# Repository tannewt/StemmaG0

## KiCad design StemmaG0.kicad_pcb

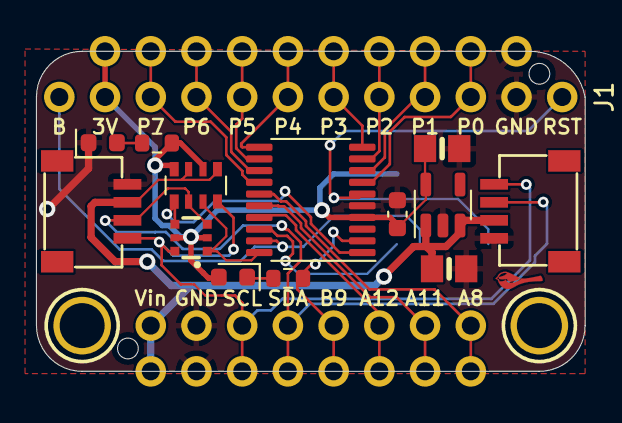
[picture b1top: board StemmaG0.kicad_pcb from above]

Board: 2 copper layers, 30.5 x 17.8 mm, 20 parts (1 on the bottom side), 24 nets.

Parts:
C1: 0.1uF; C_0603_1608Metric
C2, C3: 10uF; 0805-NO
CONN3, CONN4: SM04B-SRSS-TB; JST_SH4
D1, D2: LED_Small; LED_0603_1608Metric
J1: Conn_01x12; PinHeader_1x12_P2.54mm_Vertical
J2, J4: Conn_01x08; PinHeader_1x08_P2.54mm_Vertical
J3: Conn_ARM_JTAG_SWD_10; PinHeader_2x05_P1.27mm_Vertical_SMD
J5: Conn_01x10; PinHeader_1x10_P2.54mm_Vertical
Q2: BSS138BKS; SOT363
R1: 10K; R_0603_1608Metric
R2: R_Small; R_0603_1608Metric
R3: 10K; R_Array_Convex_4x0603
U1: STMG0x0F; TSSOP-20_4.4x6.5mm_P0.65mm
U2: AP2112K-3.3; TSOT-23-5
U$19, U$21: MOUNTINGHOLE2.5; MOUNTINGHOLE_2.5_PLATED

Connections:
3.3V: C1.1, C3.1, D2.2 (A), J1.11, J3.1 (VTref), J5.10, Q2.2 (G), Q2.5 (G), R1.1, R3.2 (1), R3.4 (1), U1.4 (VDD/VDDA), U2.5 (OUT)
/A8: J2.8, J4.8, U1.15 (PB0/PB1/PB2/PA8)
/A11: J2.7, J4.7, U1.16 (PA11[PA9])
/A12: J2.6, J4.6, U1.17 (PA12[PA10])
/B9: J2.5, J4.5, R2.2, U1.2 (PB9/PC14-OSC32_IN)
/P0: J1.3, J5.2, U1.7 (PA0)
/P1: J1.4, J5.3, U1.8 (PA1)
/P2: J1.5, J5.4, U1.9 (PA2)
/P3: J1.6, J5.5, U1.10 (PA3)
/P4: J1.7, J5.6, U1.11 (PA4)
/P5: J1.8, J5.7, U1.12 (PA5)
/P6: J1.9, J5.8, U1.13 (PA6)
/P7: J1.10, J5.9, U1.14 (PA7)
/SCL: CONN3.4 (SCL), CONN4.4 (SCL), J2.3, J4.3, Q2.6 (D), R3.8 (2)
/SCL_3V: Q2.1 (S), R3.7 (2), U1.20 (PB3/PB4/PB5/PB6/I2C1_SCL)
/SDA: CONN3.3 (SDA), CONN4.3 (SDA), J2.4, J4.4, Q2.3 (D), R3.6 (2)
/SDA_3V: Q2.4 (S), R3.5 (2), U1.1 (PB7/PB8/I2C1_SDA)
/SWCLK: J1.12, J3.4 (SWDCLK/TCK), U1.19 (PA15/PA14/SWCLK-BOOT0)
/SWDIO: J3.2 (SWDIO/TMS), U1.18 (PA13/SWDIO)
/nRST: J1.1, J3.10 (~RESET), U1.6 (NRST)
GND: C1.2, C2.2, C3.2, CONN3.1 (GND), CONN4.1 (GND), D1.1 (K), J1.2, J2.2, J3.3 (GND), J3.5 (GND), J3.9 (GNDDetect), J4.2, J5.1, U1.5 (VSS/VSSA), U2.2 (GND)
unnamed: D1.2 (A), R1.2
unnamed: D2.1 (K), R2.1
VCC: C2.1, CONN3.2 (V+), CONN4.2 (V+), J2.1, J4.1, R3.1, R3.3 (1), U2.1 (IN), U2.3 (EN)

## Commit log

2022-11-11 Initial prototype version
